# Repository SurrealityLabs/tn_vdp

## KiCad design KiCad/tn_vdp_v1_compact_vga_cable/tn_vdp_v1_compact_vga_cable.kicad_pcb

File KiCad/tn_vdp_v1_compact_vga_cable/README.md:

# TMS9918A compatible VDP based on Tang Nano 9k - Compact (SMD) version for VGA cable

This version is a compact variant of the tn_vdp_v1 board that directly
fits into the VDP socket of the TI-99/4A.  It uses SMD components and
has the same size as the Tang Nano 9k board.  It connects to a VGA 
extension cable acquired from Aliexpress, which uses a 12-pin JST PH
connector on one end.

The board routing has been updated to use 6mil traces and 6mil
spacing, making it compatible with OSHPark for manufacturing.

## BOM

|Item|Qty|Reference(s)|Value       |Description                              |Part Number            |Footprint|URL                                                               |
|----|---|------------|------------|-----------------------------------------|-----------------------|---------|------------------------------------------------------------------|
|1   |1  |            |Tang Nano 9k|FPGA development board                   |                       |         |https://wiki.sipeed.com/hardware/en/tang/Tang-Nano-9K/Nano-9K.html|
|2   |1  |U1          |1G08        |Single AND gate                          |SN74LVC1G08            |SOT-23-5 |http://www.ti.com/lit/sg/scyt129e/scyt129e.pdf                    |
|3   |1  |U4          |74LCX16245  |16 bit buffer                            |74LCX16245MTD          |TSSOP-48 |https://www.onsemi.com/pdf/datasheet/mc74lcx16245-d.pdf           |
|4   |1  |D1          |D_Schottky  |Schottky diode                           |MBR0530                |SOD-123  |                                                                  |
|5   |3  |R1, R5, R9  |4.7K        |Resistor SMD 0603                        |                       |0603     |                                                                  |
|6   |3  |R2, R6, R10 |2.2K        |Resistor SMD 0603                        |                       |0603     |                                                                  |
|7   |3  |R3, R7, R11 |1K          |Resistor SMD 0603                        |                       |0603     |                                                                  |
|8   |3  |R4, R8, R12 |470         |Resistor SMD 0603                        |                       |0603     |                                                                  |
|9   |2  |R13, R14    |47          |Resistor SMD 0603                        |                       |0603     |                                                                  |
|10  |1  |C1          |100nF       |Capacitor SMD 0603                       |                       |0603     |                                                                  |
|11  |21 |J1          |            |PCB pin Mill-Max                         |3157-0-00-15-00-00-03-0|         |                                                                  |
|12  |1  |J2          |VGA         |12-pin JST PH connector for VGA cable    |B12B-PH-K-S(LF)(SN)    |         |                                                                  |

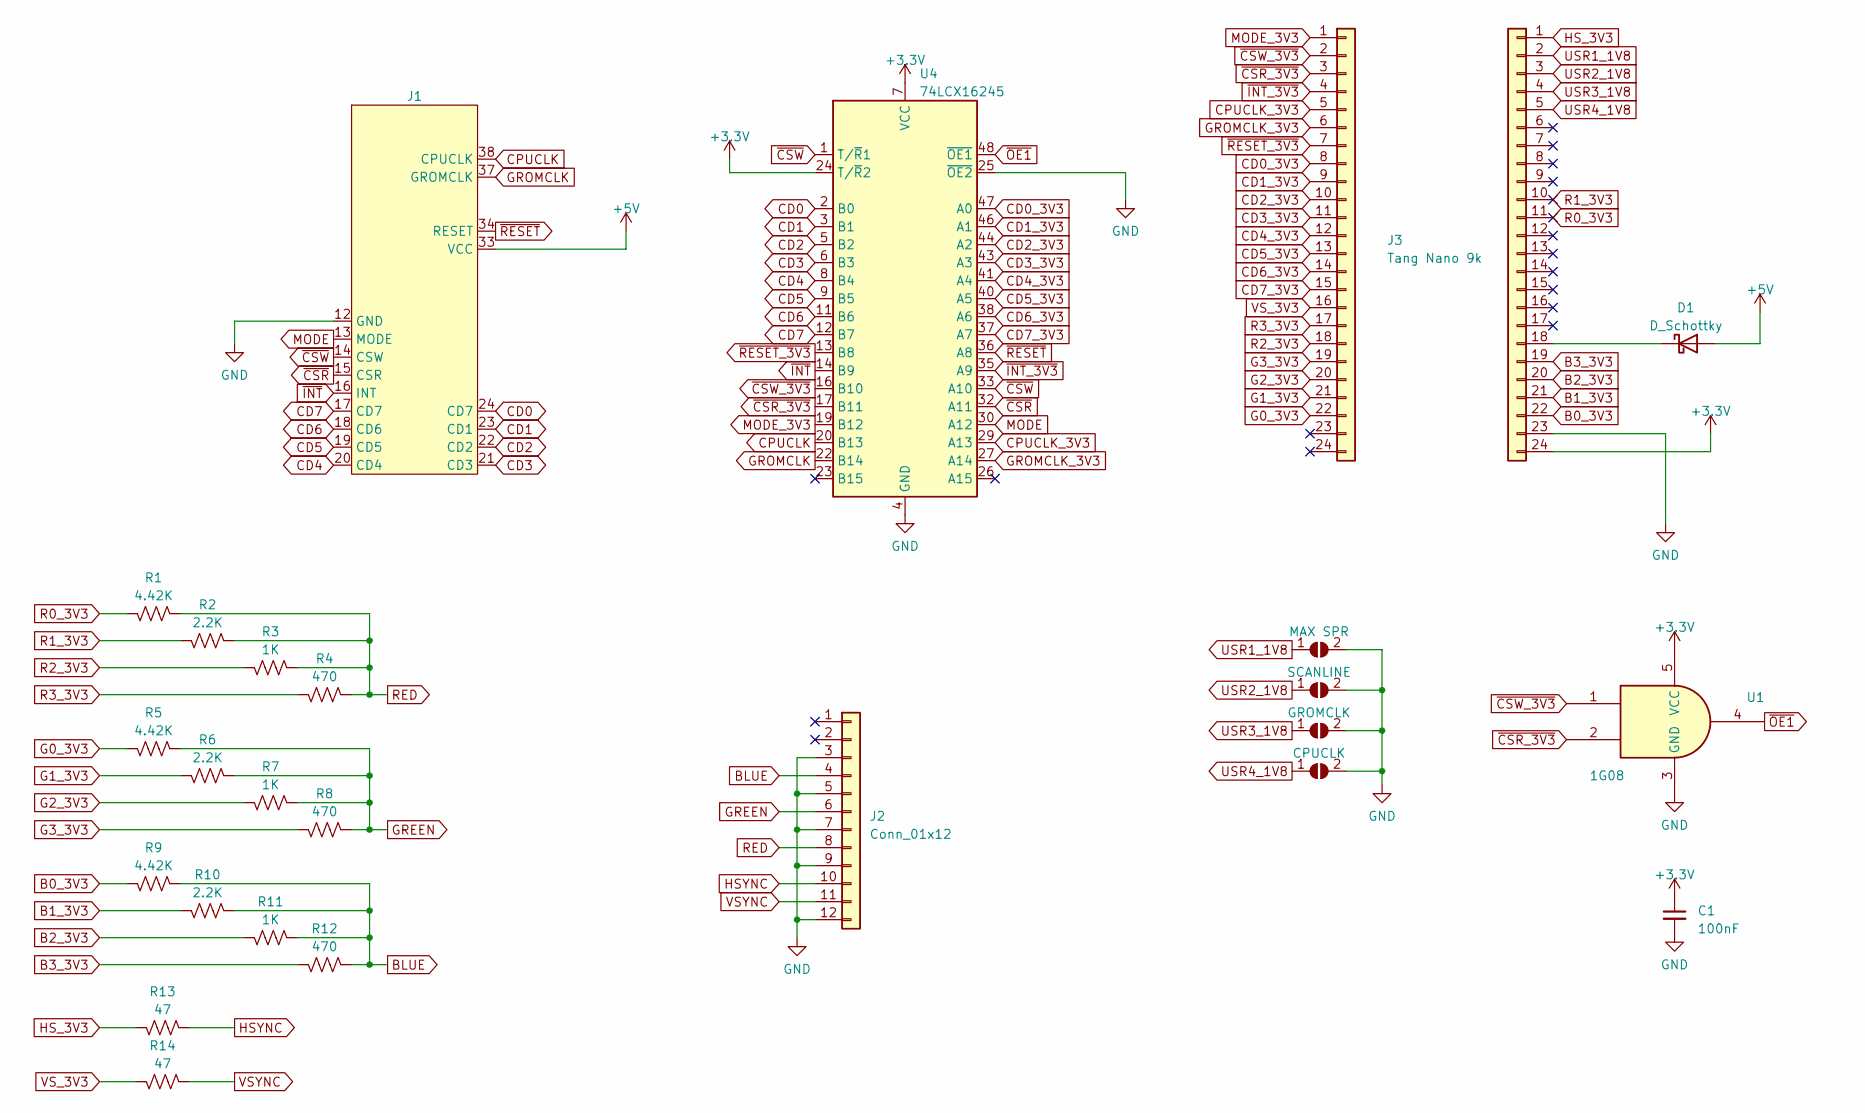
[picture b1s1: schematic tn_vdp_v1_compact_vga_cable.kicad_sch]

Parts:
C1: 100nF; C_0603_1608Metric_Pad1.08x0.95mm_HandSolder; LCSC C2857981
D1: D_Schottky; D_SOD-123; LCSC C2900723
J1: TMS99xxA_Replacement
J2: Conn_01x12; JST_PH_B12B-PH-K_1x12_P2.00mm_Vertical
J3: Tang Nano 9k; PinSocket_1x24_P2.54mm_Vertical
J4: TN9k/2; PinSocket_1x24_P2.54mm_Vertical
JP1: MAX SPR; SolderJumper-2_P1.3mm_Open_RoundedPad1.0x1.5mm
JP2: SCANLINE; SolderJumper-2_P1.3mm_Open_RoundedPad1.0x1.5mm
JP3: GROMCLK; SolderJumper-2_P1.3mm_Open_RoundedPad1.0x1.5mm
JP4: CPUCLK; SolderJumper-2_P1.3mm_Open_RoundedPad1.0x1.5mm
R1, R5, R9: 4.42K; R_0603_1608Metric_Pad0.98x0.95mm_HandSolder; LCSC C5140130
R2, R6, R10: 2.2K; R_0603_1608Metric_Pad0.98x0.95mm_HandSolder; LCSC C3016472
R3, R7, R11: 1K; R_0603_1608Metric_Pad0.98x0.95mm_HandSolder; LCSC C3016283
R4, R8, R12: 470; R_0603_1608Metric_Pad0.98x0.95mm_HandSolder; LCSC C103660
R13, R14: 47; R_0603_1608Metric_Pad0.98x0.95mm_HandSolder; LCSC C3016437
U1: 1G08; SOT-23-5_HandSoldering; LCSC C7666
U4: 74LCX16245; TSSOP-48_6.1x12.5mm_P0.5mm; LCSC C894789

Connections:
+3.3V: C1.1, J4.24, U1.5 (VCC), U4.7 (VCC), U4.18 (VCC), U4.24 (T/~R2), U4.31 (VCC), U4.42 (VCC)
+5V: D1.2 (A), J1.33 (VCC)
B0_3V3: J4.22, R9.2
B1_3V3: J4.21, R10.2
B2_3V3: J4.20, R11.2
B3_3V3: J4.19, R12.2
BLUE: J2.4, R9.1, R10.1, R11.1, R12.1
CD0: J1.24 (CD7), U4.2 (B0)
CD0_3V3: J3.8, U4.47 (A0)
CD1: J1.23 (CD1), U4.3 (B1)
CD1_3V3: J3.9, U4.46 (A1)
CD2: J1.22 (CD2), U4.5 (B2)
CD2_3V3: J3.10, U4.44 (A2)
CD3: J1.21 (CD3), U4.6 (B3)
CD3_3V3: J3.11, U4.43 (A3)
CD4: J1.20 (CD4), U4.8 (B4)
CD4_3V3: J3.12, U4.41 (A4)
CD5: J1.19 (CD5), U4.9 (B5)
CD5_3V3: J3.13, U4.40 (A5)
CD6: J1.18 (CD6), U4.11 (B6)
CD6_3V3: J3.14, U4.38 (A6)
CD7: J1.17 (CD7), U4.12 (B7)
CD7_3V3: J3.15, U4.37 (A7)
CPUCLK: J1.38 (CPUCLK), U4.20 (B13)
CPUCLK_3V3: J3.5, U4.29 (A13)
G0_3V3: J3.22, R5.2
G1_3V3: J3.21, R6.2
G2_3V3: J3.20, R7.2
G3_3V3: J3.19, R8.2
GND: C1.2, J1.12 (GND), J2.3, J2.5, J2.7, J2.9, J2.12, J4.23, JP1.2 (B), JP2.2 (B), JP3.2 (B), JP4.2 (B), U1.3 (GND), U4.4 (GND), U4.10 (GND), U4.15 (GND), U4.21 (GND), U4.25 (~OE2), U4.28 (GND), U4.34 (GND), U4.39 (GND), U4.45 (GND)
GREEN: J2.6, R5.1, R6.1, R7.1, R8.1
GROMCLK: J1.37 (GROMCLK), U4.22 (B14)
GROMCLK_3V3: J3.6, U4.27 (A14)
HSYNC: J2.10, R13.1
HS_3V3: J4.1, R13.2
MODE: J1.13 (MODE), U4.30 (A12)
MODE_3V3: J3.1, U4.19 (B12)
unnamed: D1.1 (K), J4.18
R0_3V3: J4.11, R1.2
R1_3V3: J4.10, R2.2
R2_3V3: J3.18, R3.2
R3_3V3: J3.17, R4.2
RED: J2.8, R1.1, R2.1, R3.1, R4.1
USR1_1V8: J4.2, JP1.1 (A)
USR2_1V8: J4.3, JP2.1 (A)
USR3_1V8: J4.4, JP3.1 (A)
USR4_1V8: J4.5, JP4.1 (A)
VSYNC: J2.11, R14.1
VS_3V3: J3.16, R14.2
~CSR_3V3: J3.3, U1.2, U4.17 (B11)
~CSR: J1.15 (CSR), U4.32 (A11)
~CSW_3V3: J3.2, U1.1, U4.16 (B10)
~CSW: J1.14 (CSW), U4.1 (T/~R1), U4.33 (A10)
~INT_3V3: J3.4, U4.35 (A9)
~INT: J1.16 (INT), U4.14 (B9)
~OE1: U1.4, U4.48 (~OE1)
~RESET_3V3: J3.7, U4.13 (B8)
~RESET: J1.34 (RESET), U4.36 (A8)

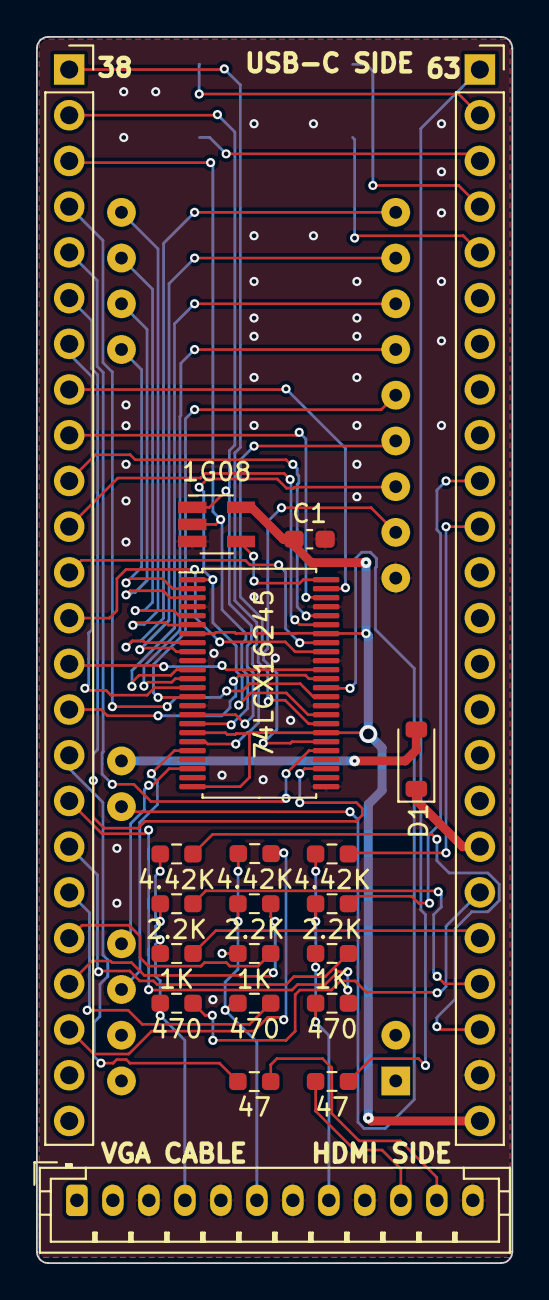
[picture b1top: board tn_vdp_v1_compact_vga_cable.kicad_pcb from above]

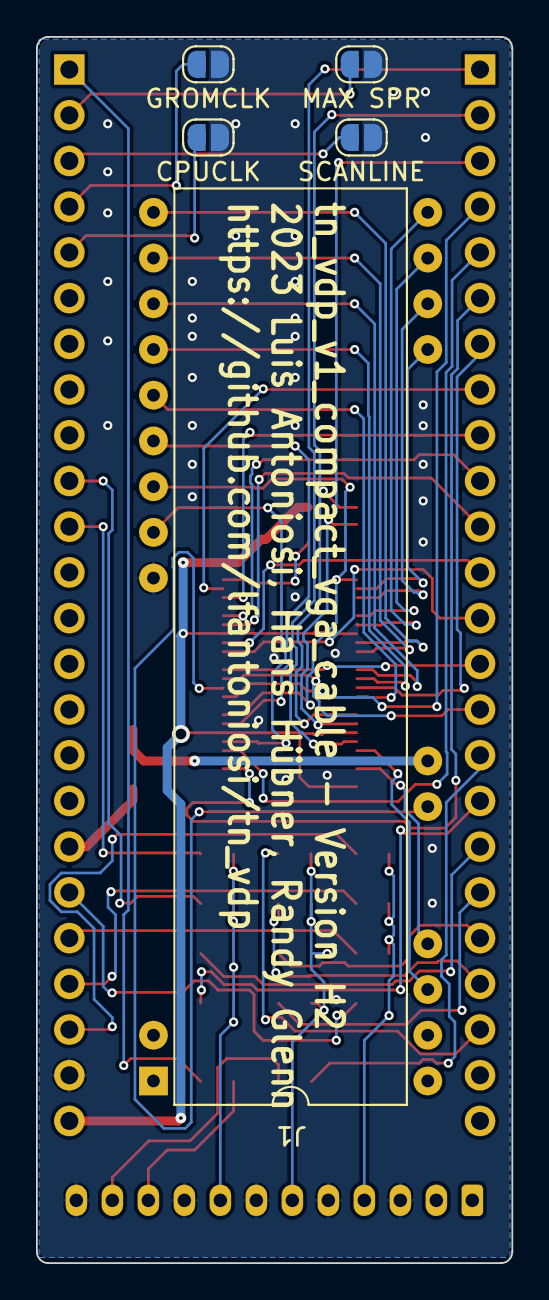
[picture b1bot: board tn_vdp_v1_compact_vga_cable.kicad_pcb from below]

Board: 2 copper layers, 26.4 x 68.1 mm, 26 parts (4 on the bottom side), 58 nets.

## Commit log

2023-06-11 Adding compact variant that uses 12-pin JST PH VGA cable
